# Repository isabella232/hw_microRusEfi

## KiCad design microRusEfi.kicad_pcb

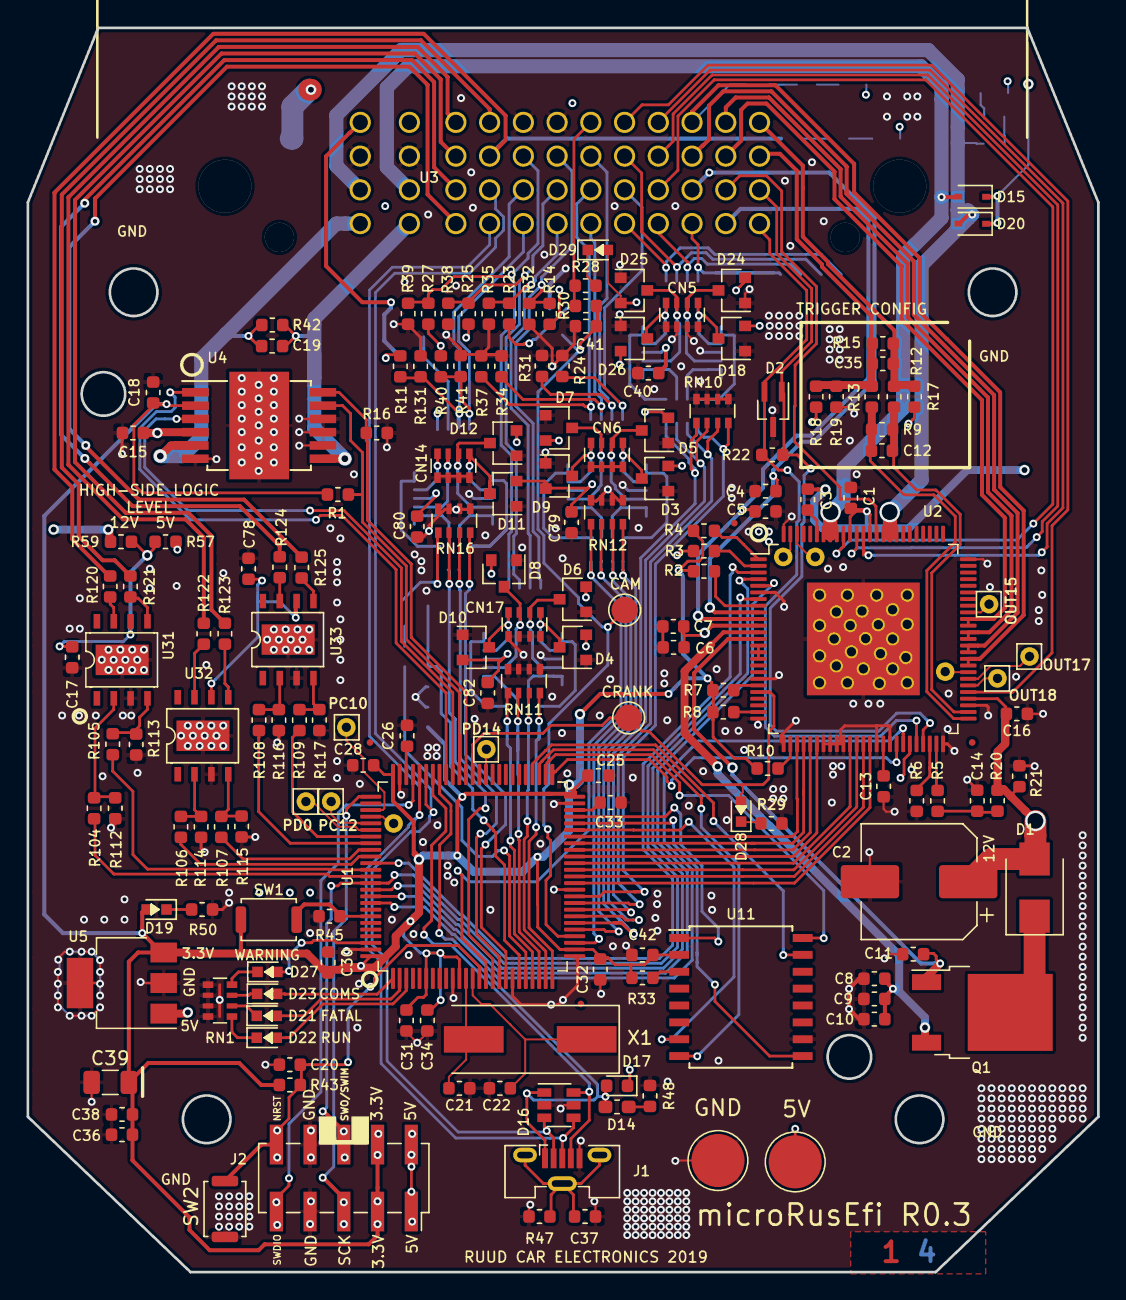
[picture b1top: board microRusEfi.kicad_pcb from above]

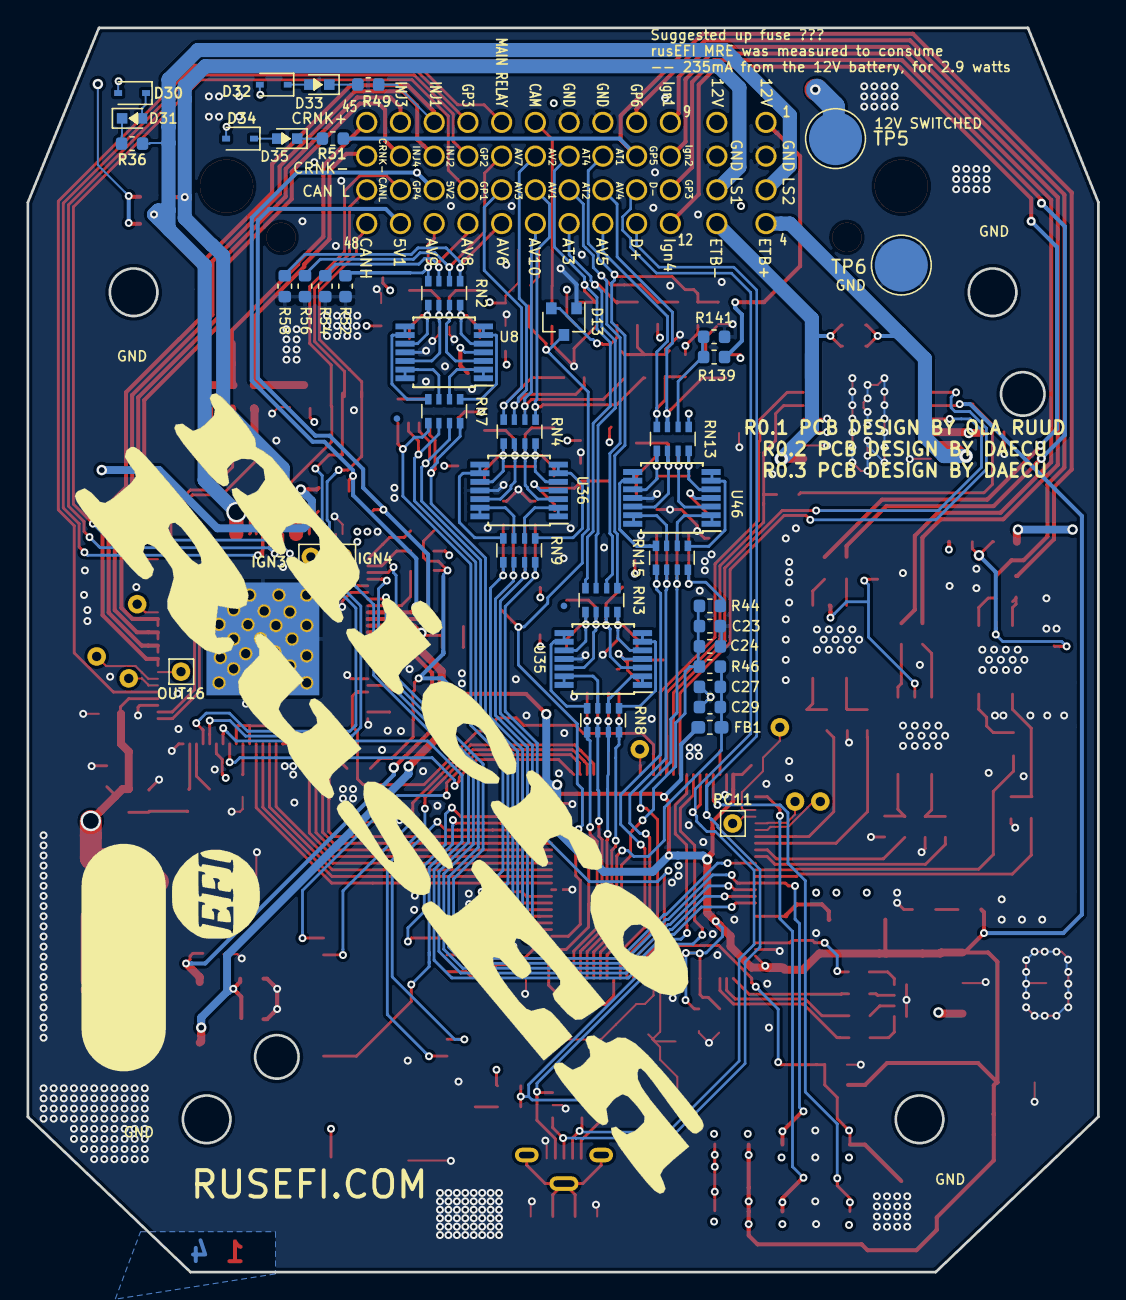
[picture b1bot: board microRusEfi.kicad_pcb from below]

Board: 4 copper layers, 80.6 x 93.7 mm, 222 parts (44 on the bottom side), 202 nets.

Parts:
C1, C6, C10, C13, C14, C15, C16, C18, C37, C38, C42: 100nF; C_0603_1608Metric
C2: 100UF 50V; CP_Elec_8x10.5
C3, C11: 4.7nF; C_0603_1608Metric
C4, C5: 470nF; C_0603_1608Metric
C7, C8, C9: 10uF; C_0603_1608Metric
C12, C35, C41: 1nF; C_0603_1608Metric
C17, C19, C20, C24, C28, C29, C30, C31, C32, C33, C34, C40, C78, C79, C80, C82: 10nF; C_0603_1608Metric
C21, C22: 4.7pF; C_0603_1608Metric
C23, C27, C36: 1uF; C_0603_1608Metric
C25, C26: 2.2uF; C_0603_1608Metric
C39: 15uF; C_1206_3216Metric
CN5, CN6, CN14, CN17: 10nF; R_Array_Convex_4x0603
D1: MBRS3200T3G; D_SMB
D2: PESD1CAN-UX; SOT-323_SC-70_Handsoldering
D3, D4, D5, D6, D7, D8, D9, D10, D11, D12, D13, D18, D24, D25, D26: BAS70-04; SOT-23
D14: LED-GREEN; C_0603_1608Metric_Pad1.05x0.95mm_HandSolder
D15, D20, D30, D32, D34: NSR0530HT; D_SOD-323
D16: ESDA6V1BC6; SOT-23-6
D17: DIODESCH; D_0603_1608Metric
D19, D21, D31, D33, D35: LED-RED; LED-0603-rusEFI
D22: LED-GRN; LED-0603-rusEFI
D23, D28, D29: LED-BLUE; LED-0603-rusEFI
D27: LED-ORG; LED-0603-rusEFI
FB1: FILTER; R_0603_1608Metric_Pad1.05x0.95mm_HandSolder
FID1, FID2, FID3, FID4, FID5, FID6: Fiducial; Fiducial_0.5mm_Mask1mm
IGN3: IGN3; Pin_D0.7mm_L6.5mm_W1.8mm_FlatFork
IGN4: IGN4; Pin_D0.7mm_L6.5mm_W1.8mm_FlatFork
J1: USB_B_Micro; USB_Micro-B_Molex-105133-0031
J2: Conn_02x05_Odd_Even; PinSocket_2x05_P2.54mm_Vertical_SMD
LOGO1: DNP; LogoMRE
LOGO2: DNP; LOGO
NT1, NT2: Net-Tie_2; Net-Tie_2_8.5mil
OUT15: OUT15; Pin_D0.7mm_L6.5mm_W1.8mm_FlatFork
OUT16: OUT16; Pin_D0.7mm_L6.5mm_W1.8mm_FlatFork
OUT17: OUT17; Pin_D0.7mm_L6.5mm_W1.8mm_FlatFork
OUT18: OUT18; Pin_D0.7mm_L6.5mm_W1.8mm_FlatFork
PC10: PC10; Pin_D0.7mm_L6.5mm_W1.8mm_FlatFork
PC11: PC11; Pin_D0.7mm_L6.5mm_W1.8mm_FlatFork
PC12: PC12; Pin_D0.7mm_L6.5mm_W1.8mm_FlatFork
PD0: PD0; Pin_D0.7mm_L6.5mm_W1.8mm_FlatFork
PD14: PD14; Pin_D0.7mm_L6.5mm_W1.8mm_FlatFork
Q1: IPD30N06S2L-23; TO-252-2
R1, R12, R13, R16, R33, R43, R45, R141: 10k; R_0603_1608Metric
R2, R3, R4, R8, R10, R42: 4.7k; R_0603_1608Metric
R5, R6, R7, R44, R59: 0R; R_0603_1608Metric
R9: 5.11k; R_0603_1608Metric
R11, R17, R18, R19, R40, R46, R57: DNP; R_0603_1608Metric
R14, R20, R21, R23, R25, R27: 2.7k; R_0603_1608Metric
R15: 15k; R_0603_1608Metric
R22: 120; R_0603_1608Metric
R24, R31, R32, R34, R35, R37, R38, R39, R41, R52, R54, R56, R58, R131: 500k; R_0603_1608Metric
R28: 2.2k; R_0603_1608Metric
R29, R36, R48, R49, R51, R112, R113, R114, R115, R116, R117: 1k; R_0603_1608Metric
R30: 33k; R_0603_1608Metric
R47: 100k; R_0603_1608Metric
R50: 680; R_0603_1608Metric
R104, R105, R106, R107, R108, R109: 20R; R_0603_1608Metric
R120, R121, R122, R123, R124, R125: 100; R_0603_1608Metric
R139: 39k; R_0603_1608Metric
RN1, RN7, RN8, RN9, RN15: 1k; R_Array_Convex_4x0603
RN2, RN3, RN4, RN13: 10k; R_Array_Convex_4x0603
RN10, RN11, RN12, RN16: 1.5k; R_Array_Convex_4x0603
SW1, SW2: SW_Push; SW_Push_SPST_NO_Alps_SKRK
TP1, TP5: 5V; TestPoint_Pad_D4.0mm
TP2, TP6: GND; TestPoint_Pad_D4.0mm
TP3, TP4: TP; TestPoint_Pad_D2.0mm
U1: STM32F767VITx; LQFP-100_14x14mm_P0.5mm
U2: TLE8888QK; LQFP-100_14x14mm_P0.5mm_THERMAL
U3: Molex_48_pin; Molex_48
U4: TLE9201SG; Infineon_PG-DSO-12-11
U5: LM2937; SOT-223
U8, U35, U36, U46: MCP6004; TSSOP-14_4.4x5mm_P0.65mm
U11: IS25WP256D-xM; SOIC-16W_7.5x10.3mm_P1.27mm
U31, U32, U33: TC4427; DFN-8-1EP_6x5mm_P1.27mm_EP4x2mm
X1: 8MHz; Crystal_SMD_HC49-SD

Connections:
/5V: C6.1, C7.1, C40.1, C78.1, C79.1, C80.1, C82.1, D3.2, D4.2, D5.2, D6.2, D7.2, D8.2, D9.2, D10.2, D11.2, D12.2, D13.2, D17.1, D18.2, D24.2, D25.2, D26.2, D29.2, D30.2, D32.2, D34.2, J2.1, J2.2, R3.2, R11.2, R14.2, R17.1, R18.1, R23.2, R25.2, R27.2, R40.2, R57.2, RN13.1, TP1.1, U2.11, U2.45, U5.1, U8.4, U32.6, U33.6, U35.4, U36.4, U46.4
/5V1: C5.1, U2.10, U3.44
/5V2: C4.1, U2.9, U3.39
/12V-SWITCH: C1.1, C2.1, C3.1, C15.1, C16.1, D1.2, D15.1, D20.1, R20.2, R21.2, R59.1, R139.2, TP5.1, U2.54, U2.87, U2.90, U3.1, U3.5, U4.4
/AT1: R27.1, R39.1, RN3.1, U3.18
/AT1_MCU: RN8.8, RN11.1, U1.22
/AT2: R25.1, R38.1, RN3.2, U3.23
/AT2_MCU: RN8.7, RN11.2, U1.23
/AT3: R23.1, R35.1, RN3.3, U3.24
/AT3_MCU: RN8.6, RN11.3, U1.24
/AT4: R14.1, R32.1, RN3.4, U3.22
/AT4_MCU: RN8.5, RN11.4, U1.25
/AV1: R37.1, RN4.1, U3.27
/AV1_MCU: RN9.8, RN12.1, U1.15
/AV2: R31.1, RN4.3, U3.26
/AV2_MCU: RN9.6, RN12.3, U1.30
/AV3: R24.1, RN4.4, U3.31
/AV3_MCU: RN9.5, RN12.4, U1.31
/AV4: R11.1, R131.1, RN13.3, U3.19
/AV4_MCU: RN15.6, RN16.3, U1.17
/AV5: R40.1, R41.1, RN13.4, U3.20
/AV5_MCU: RN15.5, RN16.4, U1.18
/AV6: R58.1, RN2.1, U3.32
/AV6_MCU: RN7.8, RN10.1, U1.32
/AV7: R56.1, RN2.2, U3.30
/AV7_MCU: RN7.7, RN10.2, U1.33
/AV8: R54.1, RN2.3, U3.36
/AV8_MCU: RN7.6, RN10.3, U1.34
/AV9: R52.1, RN2.4, U3.40
/AV9_MCU: RN7.5, RN10.4, U1.35
/AV10: R34.1, RN4.2, U3.28
/AV10_MCU: RN9.7, RN12.2, U1.28
/CAM_MCU: C41.1, D13.3, R30.1, TP3.1, U1.29
/CAM_SENSOR: R28.1, R30.2, U3.25
/CANH: D2.2, R22.1, U2.46, U3.48
/CANL: D2.1, R22.2, U2.47, U3.47
/CRANK: D28.2, TP4.1, U1.63, U2.21
/CRNK+: C35.1, R12.1, R15.1, R17.2, U3.45
/CRNK-: C35.2, R13.1, R15.2, R18.2, R19.2, U3.46
/CS_TLE: U1.86, U2.3
/E-THROTTLE+: C19.2, R42.2, U3.4, U4.5
/E-THROTTLE-: C19.1, R42.1, U3.8, U4.7
/FlashMemory/CS: U1.45, U11.7
/FlashMemory/HOLD: U1.47, U11.1
/GP1: U2.91, U3.35
/GP2: U2.89, U3.34
/GP3: U2.88, U3.33
/GP4: U2.86, U3.43
/GP5: R51.2, R120.1, U3.14
/GP6: R121.1, U3.13
/H-BRIDGE/DIR: U1.67, U4.1
/H-BRIDGE/DIS: R1.2, U1.65, U4.11
/INJECTOR-1: R49.2, U2.59, U2.60, U3.37
/INJECTOR-2: U2.61, U2.62, U3.38
/INJECTOR-3: U2.63, U2.64, U3.41
/INJECTOR-4: U2.65, U2.66, U3.42
/Ign1: R122.1, U3.9
/Ign2: R123.1, U3.10
/Ign3: R124.1, U3.11
/Ign4: R125.1, U3.12
/LS1: D15.2, U2.92, U2.93, U2.94, U3.7
/LS2: D20.2, R36.2, U2.83, U2.84, U2.85, U3.3
/MAIN_RELAY: U2.55, U3.29
/MCU/NRST: C20.2, J2.10, R43.2, SW2.1, U1.14
/MCU/PA9: D14.2, D16.1, D17.2, J1.1, NT1.2
/MCU/PA10: D16.6, J1.4, U1.69
/MCU/PA13: J2.9, U1.72
/MCU/PA14: J2.5, U1.76
/MCU/PB10: U1.46, U11.9
/MCU/PB13: U1.52, U11.16
/MCU/PB14: U1.53, U11.8
/MCU/PB15: U1.54, U11.15
/MCU/PC7: R16.1, U1.64, U4.12
/MCU/PC9: U1.66, U4.3
/MCU/PC10: PC10.1, U1.78
/MCU/PC11: PC11.1, U1.79
/MCU/PC12: PC12.1, U1.80
/MCU/PD0: PD0.1, U1.81
/MCU/PD14: PD14.1, U1.61
/MCU/shield: C37.1, J1.6, R47.1
/PE1: D27.2, U1.98
/PE2: D23.2, U1.1
/PE3: D21.2, U1.2
/PE4: D22.2, U1.3
/SCK: J2.6, U1.89, U2.7
/SI: U1.91, U2.5
/SO: U1.90, U2.4
/TLE8888-1QK/CAN_RX: U1.51, U2.43
/TLE8888-1QK/CAN_TX: U1.92, U2.44
/TLE8888-1QK/IGN_EN: R10.2, U2.27
/TLE8888-1QK/IGN_OUT_3: IGN3.1, U2.98
/TLE8888-1QK/IGN_OUT_4: IGN4.1, U2.99
/TLE8888-1QK/INJ_EN: R8.2, U2.24
/TLE8888-1QK/INJ_IN_1: U1.44, U2.28
/TLE8888-1QK/INJ_IN_2: U1.43, U2.29
/TLE8888-1QK/INJ_IN_3: U1.42, U2.30
/TLE8888-1QK/INJ_IN_4: U1.41, U2.31
/TLE8888-1QK/IN_9: U1.40, U2.36
/TLE8888-1QK/IN_10: U1.39, U2.37
/TLE8888-1QK/IN_11: U1.38, U2.38
/TLE8888-1QK/IN_12: U1.37, U2.39
/TLE8888-1QK/KEY: R5.2, U2.49
/TLE8888-1QK/OUT_7: U2.14, U2.15, U2.16
/TLE8888-1QK/OUT_15: OUT15.1, U2.67
/TLE8888-1QK/OUT_16: OUT16.1, U2.58
/TLE8888-1QK/OUT_17: OUT17.1, U2.57
/TLE8888-1QK/OUT_18: OUT18.1, U2.56
/TLE8888-1QK/VDDIO: R7.2, U2.20
/TLE8888-1QK/WAKE: R6.2, U2.48
/USB_D+: D16.4, J1.3, U1.71, U3.16
/USB_D-: D16.3, J1.2, U1.70, U3.15
/VDD: C18.1, C28.2, C30.2, C31.2, C32.2, C33.2, C34.2, C36.2, C38.1, C39.2, C42.2, D19.2, FB1.1, J2.3, J2.4, R1.1, R2.2, R4.2, R7.1, R8.1, R10.1, R33.1, R43.1, SW1.1, U1.6, U1.11, U1.27, U1.50, U1.75, U1.100, U4.2, U5.3, U11.2
/Vbat_MCU: RN15.7, RN16.2, U1.16
/Vref: R44.1, RN15.8, RN16.1
/hi-lo/GP5_MCU: R104.2, U1.88
/hi-lo/GP6_MCU: R105.2, U1.87
/hi-lo/Ign1_MCU: R106.2, U1.85
/hi-lo/Ign2_MCU: R107.2, U1.84
/hi-lo/Ign3_MCU: R108.2, U1.83
/hi-lo/Ign4_MCU: R109.2, U1.82
GND: C1.2, C2.2, C4.2, C5.2, C6.2, C7.2, C8.2, C9.2, C10.2, C11.2, C13.2, C14.2, C15.2, C16.2, C17.2, C18.2, C20.1, C21.2, C22.2, C23.1, C24.1, C25.2, C26.2, C27.1, C28.1, C29.1, C30.1, C31.1, C32.1, C33.1, C34.1, C36.1, C37.2, C38.2, C39.1, C40.2, C41.2, C42.1, C78.2, C79.2, C80.2, C82.2, CN5.5, CN5.6, CN5.7, CN5.8, CN6.5, CN6.6, CN6.7, CN6.8, CN14.5, CN14.6, CN14.7, CN14.8, CN17.5, CN17.6, CN17.7, CN17.8, D2.3, D3.1, D4.1, D5.1, D6.1, D7.1, D8.1, D9.1, D10.1, D11.1, D12.1, D13.1, D16.2, D16.5, D18.1, D24.1, D25.1, D26.1, J1.5, J2.7, J2.8, NT2.2, R6.1, R16.2, R19.1, R21.1, R24.2, R29.2, R31.2, R32.2, R34.2, R35.2, R37.2, R38.2, R39.2, R41.2, R45.2, R47.2, R48.1, R50.1, R52.2, R54.2, R56.2, R58.2, R112.1, R113.1, R114.1, R115.1, R116.1, R117.1, R131.2, R141.2, RN1.5, RN1.6, RN1.7, RN1.8, RN10.5, RN10.6, RN10.7, RN10.8, RN11.5, RN11.6, RN11.7, RN11.8, RN12.5, RN12.6, RN12.7, RN12.8, RN16.5, RN16.6, RN16.7, RN16.8, SW2.2, TP2.1, TP6.1, U1.10, U1.19, U1.26, U1.49, U1.74, U1.99, U2.6, U2.19, U2.25, U2.26, U2.32, U2.33, U2.34, U2.35, U2.40, U2.42, U2.50, U2.53, U2.75, U2.100, U2.101, U3.2, U3.6, U3.17, U3.21, U4.6, U4.8, U4.9, U4.10, U4.13, U5.2, U8.11, U11.10, U31.3, U31.9, U32.3, U32.9, U33.3, U33.9, U35.11, U36.11, U46.11
unnamed: C3.2, U2.95
unnamed: C8.1, C9.1, C10.1, Q1.3, U2.12
unnamed: C11.1, Q1.1, U2.13
unnamed: C12.1, R9.1, R12.2, U2.52
unnamed: C12.2, R9.2, R13.2, U2.51
unnamed: C13.1, U2.41
unnamed: C14.1, R5.1, R20.1
unnamed: C17.1, R57.1, R59.2, U31.6
unnamed: C21.1, U1.12, X1.2
unnamed: C22.1, U1.13, X1.1
unnamed: C23.2, C24.2, R44.2, R46.1, U1.20
unnamed: C25.1, U1.48
unnamed: C26.1, U1.73
unnamed: C27.2, C29.2, FB1.2, R46.2, U1.21
unnamed: CN5.1, D18.3, RN2.5, U8.10
unnamed: CN5.2, D24.3, RN2.6, U8.12
unnamed: CN5.3, D25.3, RN2.7, U8.3
unnamed: CN5.4, D26.3, RN2.8, U8.5
unnamed: CN6.1, D3.3, RN4.5, U36.10
unnamed: CN6.2, D5.3, RN4.6, U36.12
unnamed: CN6.3, D7.3, RN4.7, U36.3
unnamed: CN6.4, D9.3, RN4.8, U36.5
unnamed: CN14.1, D11.3, RN13.5, U46.10
unnamed: CN14.2, D12.3, RN13.6, U46.12
unnamed: CN14.3, RN13.7, U46.3
unnamed: CN14.4, RN13.8, U46.5
unnamed: CN17.1, D4.3, RN3.5, U35.10
unnamed: CN17.2, D6.3, RN3.6, U35.12
unnamed: CN17.3, D8.3, RN3.7, U35.3
unnamed: CN17.4, D10.3, RN3.8, U35.5
unnamed: D1.1, Q1.2
unnamed: D14.1, R48.2
unnamed: D19.1, R50.2
unnamed: D21.1, RN1.2
unnamed: D22.1, RN1.1
unnamed: D23.1, RN1.3
unnamed: D27.1, RN1.4
unnamed: D28.1, R29.1
unnamed: D29.1, R28.2
unnamed: D30.1, D31.2
unnamed: D31.1, R36.1
unnamed: D32.1, D33.2
unnamed: D33.1, R49.1
unnamed: D34.1, D35.2
unnamed: D35.1, R51.1
unnamed: NT1.1, U1.68
unnamed: NT2.1, U1.36
unnamed: R2.1, U2.8
unnamed: R3.1, U2.2
unnamed: R4.1, U2.1
unnamed: R33.2, U11.3
unnamed: R45.1, SW1.2, U1.94
unnamed: R104.1, R112.2, U31.2
unnamed: R105.1, R113.2, U31.4
unnamed: R106.1, R114.2, U32.2
unnamed: R107.1, R115.2, U32.4
unnamed: R108.1, R116.2, U33.2
unnamed: R109.1, R117.2, U33.4
unnamed: R120.2, U31.7
unnamed: R121.2, U31.5
unnamed: R122.2, U32.7
unnamed: R123.2, U32.5
unnamed: R124.2, U33.7
unnamed: R125.2, U33.5
unnamed: R139.1, R141.1, RN13.2
unnamed: RN7.1, U8.6, U8.7
unnamed: RN7.2, U8.1, U8.2
unnamed: RN7.3, U8.13, U8.14
unnamed: RN7.4, U8.8, U8.9
unnamed: RN8.1, U35.6, U35.7
unnamed: RN8.2, U35.1, U35.2
unnamed: RN8.3, U35.13, U35.14
unnamed: RN8.4, U35.8, U35.9
unnamed: RN9.1, U36.6, U36.7
unnamed: RN9.2, U36.1, U36.2
unnamed: RN9.3, U36.13, U36.14
unnamed: RN9.4, U36.8, U36.9
unnamed: RN15.1, U46.6, U46.7
unnamed: RN15.2, U46.1, U46.2
unnamed: RN15.3, U46.13, U46.14
unnamed: RN15.4, U46.8, U46.9

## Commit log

2019-09-02 Made silk key a bit more clear. https://github.com/rusefi/hw_microRusEfi/issues/108
2019-10-05 Added rusEFI-Micro_R0.3_JLCPCB .zip
2022-02-04 [ImgBot] Optimize images
    *Total -- 348.22kb -> 314.82kb (9.59%)
    /microRusEfi.jpg -- 154.81kb -> 136.84kb (11.61%)
    /microRusEfi_back.jpg -- 136.95kb -> 121.52kb (11.27%)
    /CKKB48-1-A_both_sides.jpg -- 56.46kb -> 56.46kb (0.01%)
